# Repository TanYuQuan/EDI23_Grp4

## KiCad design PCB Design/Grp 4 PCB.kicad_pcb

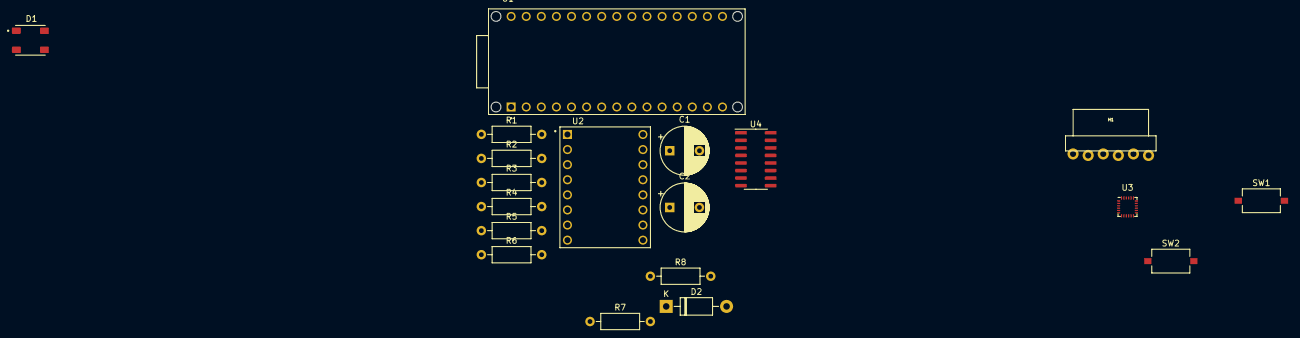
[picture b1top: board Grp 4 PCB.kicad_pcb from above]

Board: 2 copper layers, 19 parts (0 on the bottom side), 19 nets, no tracks yet.

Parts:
C1: 4.7µF; CP_Radial_D8.0mm_P5.00mm
C2: 100µF; CP_Radial_D8.0mm_P5.00mm
D1: 2758; SOL320P540X170-4N
D2: 1N4001; D_DO-41_SOD81_P10.16mm_Horizontal
H1: HC05; HC-05_BENT
R1, R2, R6: 10kΩ; R_Axial_DIN0207_L6.3mm_D2.5mm_P10.16mm_Horizontal
R3, R4: R_Variable; R_Axial_DIN0207_L6.3mm_D2.5mm_P10.16mm_Horizontal
R5: 1kΩ; R_Axial_DIN0207_L6.3mm_D2.5mm_P10.16mm_Horizontal
R7, R8: 6.6Ω; R_Axial_DIN0207_L6.3mm_D2.5mm_P10.16mm_Horizontal
SW1, SW2: SW_Push; SW_Tactile_SPST_NO_Straight_CK_PTS636Sx25SMTRLFS
U1: ABX00053; MODULE_ABX00053
U2: A4988_STEPPER_MOTOR_DRIVER_CARRIER_BLACK; MODULE_A4988_STEPPER_MOTOR_DRIVER_CARRIER_BLACK
U3: MPU-9250; InvenSense_QFN-24_3x3mm_P0.4mm
U4: HX711; SOP-16_3.9x9.9mm_P1.27mm

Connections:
+5V: C2.1, D1.1 (VDD), D2.2 (A), H1.1 (VCC), R1.1, R2.1, R3.2, R4.2, R7.2, U2.10 (VDD), U3.13 (VDD), U4.1 (VSUP)
+12V: C1.1, U2.16 (VMOT)
Earth: C1.2, C2.2, D1.3 (VSS), H1.2 (GND), R6.2, R8.2, SW1.2, SW2.2, U1.14 (GND), U1.19 (GND), U2.9 (GND), U2.15 (GND), U3.18 (GND), U4.5 (AGND)
unnamed: D1.4 (DIN), R5.1
unnamed: D2.1 (K), U1.12 (+5V)
unnamed: H1.4 (RXD), U1.16 (TX)
unnamed: H1.3 (TXD), U1.17 (RX)
unnamed: R3.1, R4.1, R6.1, U1.4 (A0/DAC0/GPIO26)
unnamed: R7.1, R8.1, U1.5 (A1/GPIO27)
unnamed: U1.8 (A4/GPIO12), U3.24 (SDA/MOSI)
unnamed: U1.9 (A5/GPIO13), U3.23 (SCL/SCLK)
unnamed: U1.21 (D3/GPIO15), U4.12 (DOUT)
unnamed: U1.22 (D4/GPIO26), U4.11 (PD_SCK)
unnamed: R5.2, U1.23 (D5/GPIO17)
unnamed: U1.24 (D6/GPIO18), U2.1 (~ENABLE)
unnamed: U1.25 (D7/GPIO19), U2.8 (DIR)
unnamed: U1.26 (D8/GPIO20), U2.7 (STEP)
unnamed: R1.2, SW1.1, U1.29 (D11/GPIO7/COPI)
unnamed: R2.2, SW2.1, U1.30 (D12/GPIO4/CIPO)

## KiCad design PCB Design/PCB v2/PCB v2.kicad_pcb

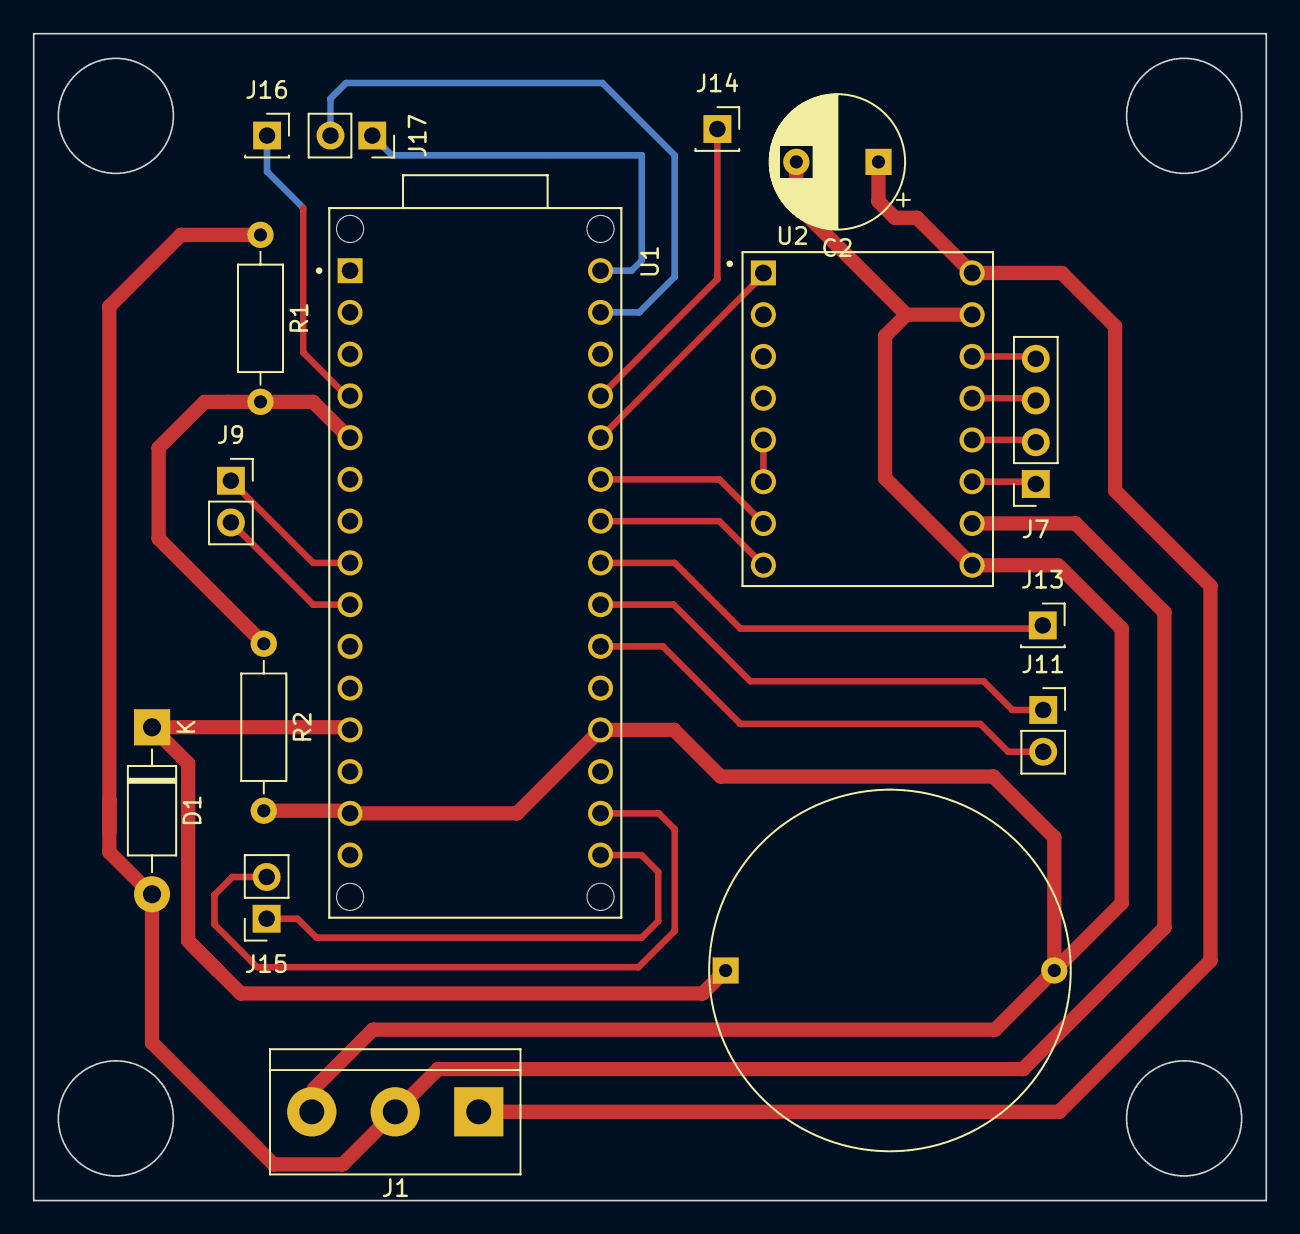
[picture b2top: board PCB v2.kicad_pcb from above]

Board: 2 copper layers, 75.0 x 71.0 mm, 16 parts (0 on the bottom side), 24 nets.

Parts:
C1: 1F; 1F Capacitor
C2: 4.7µF; CP_Radial_D8.0mm_P5.00mm
D1: 1N4001; D_DO-41_SOD81_P10.16mm_Horizontal
J1: Screw_Terminal_01x03; TerminalBlock_bornier-3_P5.08mm
J7: Conn_01x04_Socket; PinSocket_1x04_P2.54mm_Vertical
J9, J11, J15, J17: Conn_01x02_Socket; PinSocket_1x02_P2.54mm_Vertical
J13, J14, J16: Conn_01x01_Socket; PinSocket_1x01_P2.54mm_Vertical
R1, R2: 6Ω; R_Axial_DIN0207_L6.3mm_D2.5mm_P10.16mm_Horizontal
U1: ABX00053; MODULE_ABX00053
U2: A4988_STEPPER_MOTOR_DRIVER_CARRIER_BLACK; MODULE_A4988_STEPPER_MOTOR_DRIVER_CARRIER_BLACK

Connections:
unnamed: D1.2 (A), J1.2, R1.1, U2.10 (VDD)
unnamed: C1.1, D1.1 (K), U1.12 (+5V)
unnamed: C2.1, J1.1, U2.16 (VMOT)
unnamed: C1.2, C2.2, J1.3, R2.2, U1.14 (GND), U1.19 (GND), U2.9 (GND), U2.15 (GND)
unnamed: J7.1, U2.11 (1B)
unnamed: J7.2, U2.12 (1A)
unnamed: J7.3, U2.13 (2A)
unnamed: J7.4, U2.14 (2B)
unnamed: J9.1, U1.8 (A4/GPIO12)
unnamed: J9.2, U1.9 (A5/GPIO13)
unnamed: J11.1, U1.22 (D4/GPIO26)
unnamed: J11.2, U1.21 (D3/GPIO15)
unnamed: J13.1, U1.23 (D5/GPIO17)
unnamed: J14.1, U1.27 (D9/GPIO21)
unnamed: J15.1, U1.16 (TX)
unnamed: J15.2, U1.17 (RX)
unnamed: J16.1, U1.4 (A0/DAC0/GPIO26)
unnamed: J17.1, U1.30 (D12/GPIO4/CIPO)
unnamed: J17.2, U1.29 (D11/GPIO7/COPI)
unnamed: R1.2, R2.1, U1.5 (A1/GPIO27)
unnamed: U1.24 (D6/GPIO18), U2.8 (DIR)
unnamed: U1.25 (D7/GPIO19), U2.7 (STEP)
unnamed: U1.26 (D8/GPIO20), U2.1 (~ENABLE)
unnamed: U2.5 (~RESET), U2.6 (~SLEEP)

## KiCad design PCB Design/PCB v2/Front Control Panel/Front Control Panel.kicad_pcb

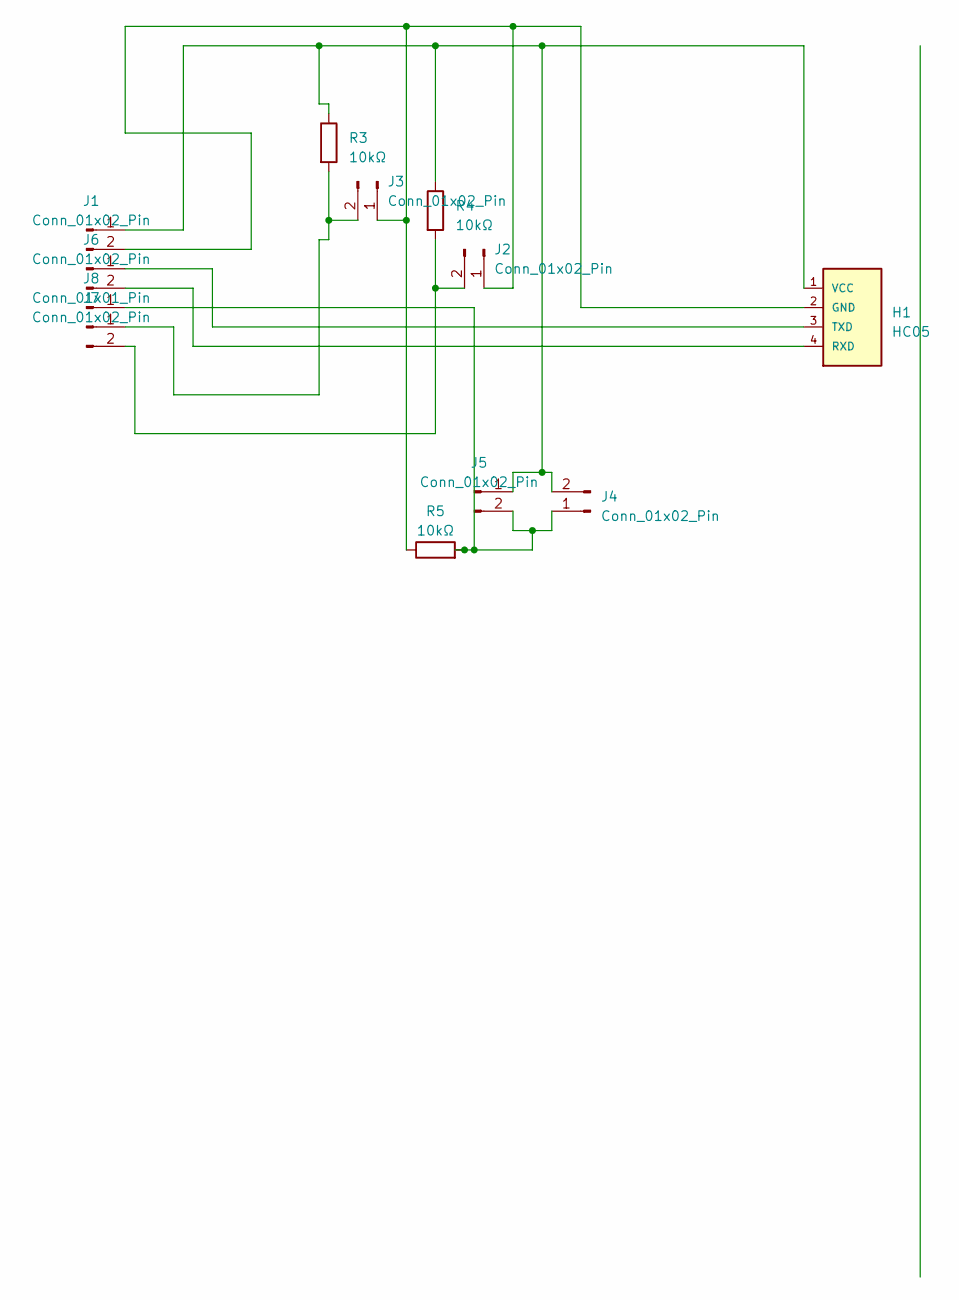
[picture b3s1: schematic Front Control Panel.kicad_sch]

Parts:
H1: HC05
J1, J2, J3, J4, J5, J6, J7: Conn_01x02_Pin; PinHeader_1x02_P2.54mm_Vertical
J8: Conn_01x01_Pin; PinHeader_1x01_P2.54mm_Vertical
R3, R4, R5: 10kΩ; R_Axial_DIN0207_L6.3mm_D2.5mm_P10.16mm_Horizontal

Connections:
unnamed: H1.2 (GND), J1.2, J2.1, J3.1, R5.1
unnamed: H1.4 (RXD), J6.2
unnamed: H1.3 (TXD), J6.1
unnamed: H1.1 (VCC), J1.1, J4.2, J5.1, R3.1, R4.1
unnamed: J2.2, J7.2, R4.2
unnamed: J3.2, J7.1, R3.2
unnamed: J4.1, J5.2, J8.1, R5.2

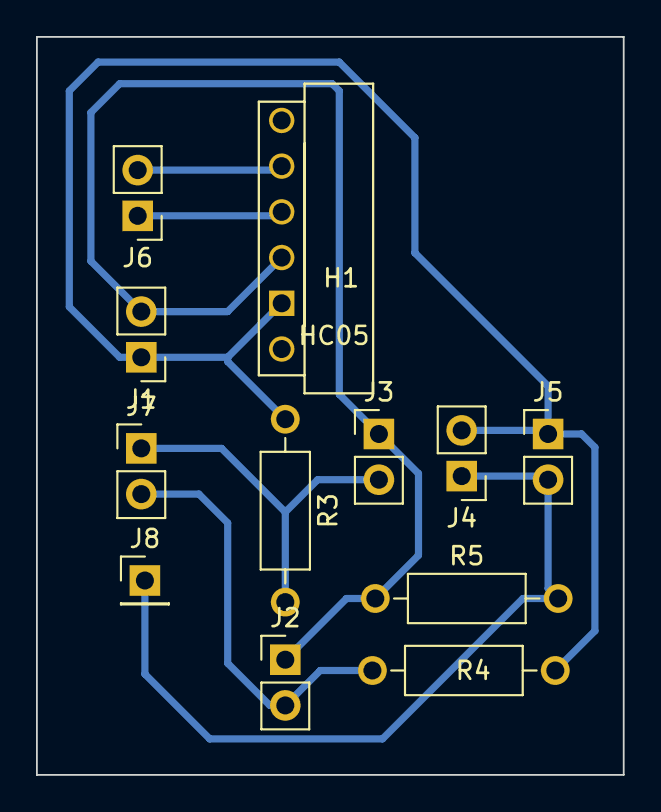
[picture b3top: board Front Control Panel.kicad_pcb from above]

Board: 2 copper layers, 32.6 x 41.0 mm, 12 parts (0 on the bottom side), 7 nets.

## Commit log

2023-03-24 Create Code for Sci Lab
2023-04-24 Create SDR
2023-04-24 PDR Update
2023-04-24 Rename Code for Sci Lab to Code for Sci Lab (Suspension Modeling)
